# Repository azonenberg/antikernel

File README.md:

# Antikernel

This is the new development repository for the Antikernel OS.

## Project Roadmap:

In no particular order...

Eventually some of these TODOs will be broken down into tickets on the issue tracker. Need to work out some finer 
details on design first.

* The legacy Splash build system is being completely rewritten and replaced.
* We'd love to write some developer documentation and formally specify the APIs for various existing components, as 
well as writing specifications for not-yet-implemented peripherals/drivers/services
* Fix the SARATOGA L1 cache so the miss servicing latency isn't so bad.
* Reduce hazards between SARATOGA execution units so we can dual-issue a higher fraction of instructions.
* Experiment with porting Antikernel to a Xilinx Zynq SoC using both the Cortex-A9s and the FPGA.
* We should probably have a filesystem at some point.

## Stuff you might be interested in:

* Project IRC channel: #antikernel on Freenode
* Original PhD thesis: https://pqdtopen.proquest.com/doc/1705867421.html?FMT=ABS
* CHES 2016 paper: https://eprint.iacr.org/2016/550
* CHES 2016 slides: http://www.chesworkshop.org/ches2016/presentations/0918%20Session%205/CHES2016_Session5_2.pdf
* CHES 2016 video: https://www.iacr.org/cryptodb/data/paper.php?pubkey=27850
* TODO: S4x17 slides and video once posted
* Build system: https://github.com/azonenberg/splash-build-system/

## NOTES

The "legacy-*" directories contain a raw export of the old Subversion repository. This will all get moved elsewhere,
possibly to separate repositories, during the upcoming restructuring.

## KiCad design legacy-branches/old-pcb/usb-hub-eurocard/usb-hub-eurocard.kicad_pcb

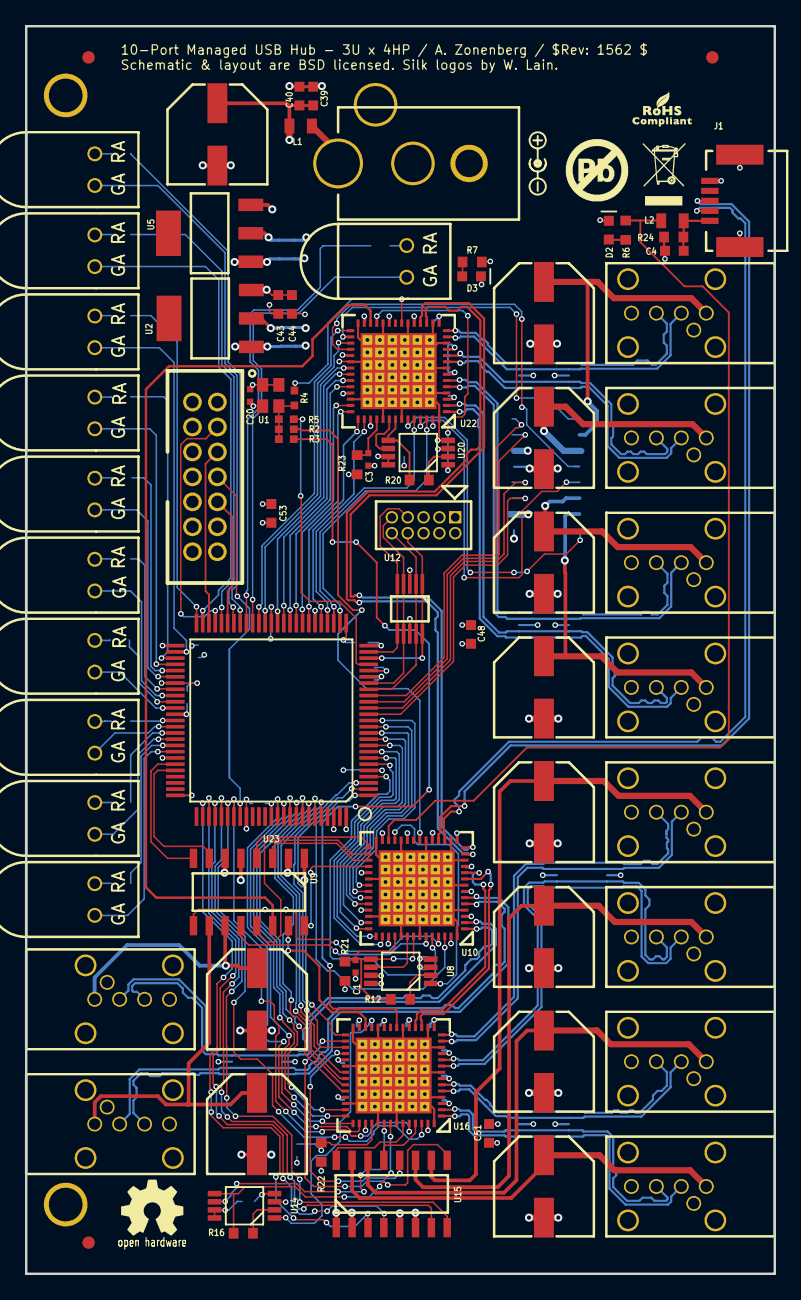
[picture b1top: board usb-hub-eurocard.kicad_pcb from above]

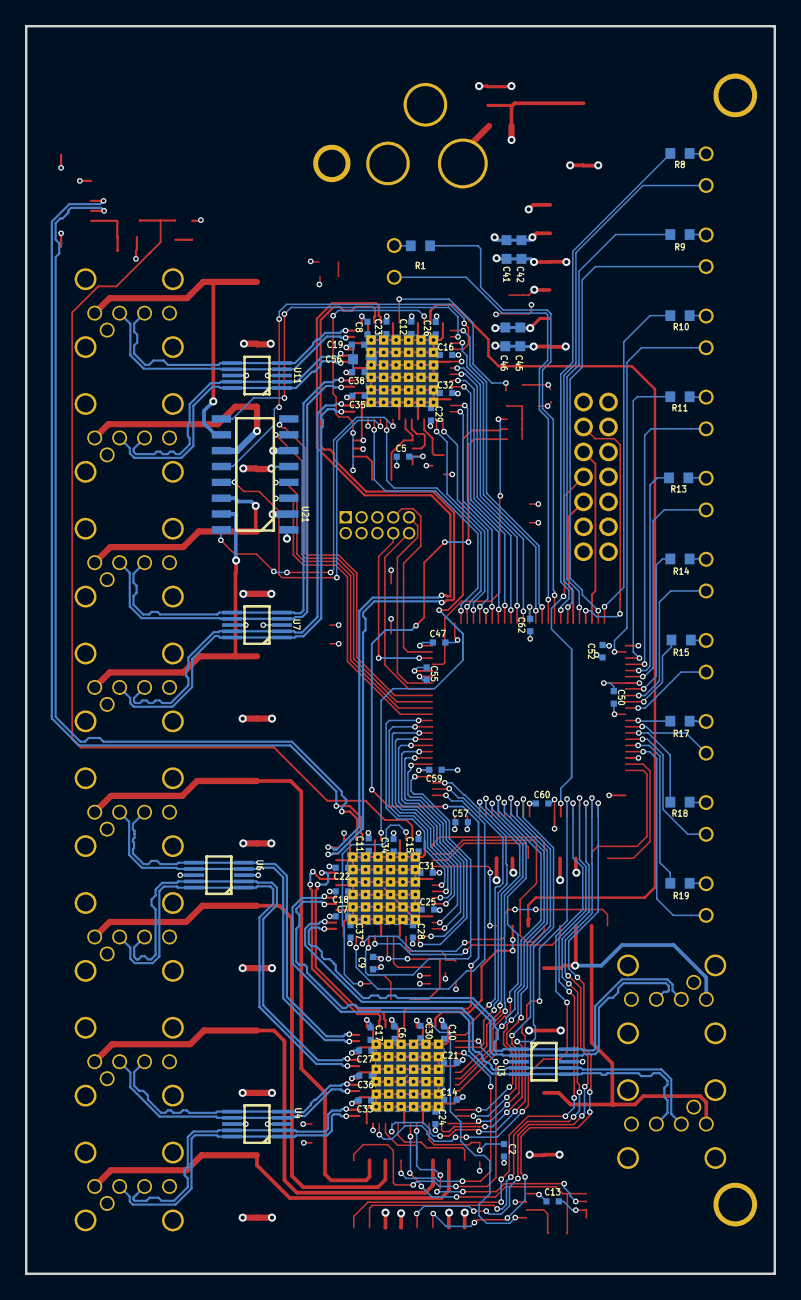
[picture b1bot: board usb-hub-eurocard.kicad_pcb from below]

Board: 4 copper layers, 60.0 x 100.0 mm, 145 parts (64 on the bottom side), 166 nets.

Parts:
C1, C2, C3, C5, C6, C7, C8, C9, C10, C11, C12, C13, C14, C15, C16, C17, C18, C19, C20, C21, C22, C23, C24, C25, C26, C27, C28, C29, C30, C31, C32, C33, C34, C35, C36, C37, C38, C47, C50, C52, C55, C57, C59, C60, C62: 0.1 uF; EIA_0402_CAP_NOSILK
C4, C39, C40, C41, C42, C43, C44, C45, C46, C48, C51, C53, C56: 4.7 uF; EIA_0603_CAP_NOSILK
C49, C54, C58, C61, C63, C64, C65, C66, C67, C68, C69: 150 uF; CAP_AL_6.3MM_SMT
D1, D4, D5, D6, D7, D8, D9, D10, D11, D12, D13: R/G; LED_INDICATOR_2.54MM_5MM_RG_RA
D2, D3: GREEN; EIA_0603_LED
FIDUCIAL_1MM, FIDUCIAL_1MM#2, FIDUCIAL_1MM#3: VAL**; FIDUCIAL_1MM
J1: USB; CONN_HIROSE_UX60S-MB-5ST_MINI_USB
J2, J3, J4, J5, J6, J8, J9, J10, J11, J12: USB_2; CONN_FCI_USB_73725-0110BLF
J7: XILINX_JTAG; XILINX_JTAG_PTH_MOLEX_0878311420
K1: DC JACK; CONN_CUI_PJ-058BH_HIPWR_BARREL_NOSLOT
L1: 120R 5A; EIA_0805_INDUCTOR_NOSILK
L2: 600R; EIA_0805_INDUCTOR_NOSILK
MECHANICAL_EUROCARD_3U_FRONTHOLES: VAL**; MECHANICAL_EUROCARD_3U_FRONTHOLES
P1: CONN_10; CONN_HEADER_1.27MM_2X5
R1, R6, R7, R8, R9, R10, R11, R13, R14, R15, R17, R18, R19: 470; EIA_0603_RES_NOSILK
R2, R3, R4, R5: 33; EIA_0402_RES_NOSILK
R12, R16, R20: 1K; EIA_0603_RES_NOSILK
R21, R22, R23, R24: 100K; EIA_0603_RES_NOSILK
U1: 24 MHz; OSCILLATOR_2.5x2.0
U2: LDO1117-18; SOT223-4
U3, U4, U6, U7, U11, U12: RCLAMP0514M; SOP_10_0.5MM_3MM
U5: LDO1117-33; SOT223-4
U8, U14, U20: 25LC080; SOP_8_0.5MM_3MM
U9, U15, U21: TPS2044BD; SOIC_16_3.9MM
U10, U16, U22: CY7C65631; QFN_56_0.5MM_8x8MM
U23: XC2C128-7VQG100C; QFP_100_0.5MM

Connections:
/1V8: C45.1, C46.1, C47.1, C50.1, U2.2, U23.26, U23.57
/3V3: C5.1, C6.1, C7.1, C8.1, C9.1, C10.1, C11.1, C12.1, C13.1, C14.1, C15.1, C16.1, C17.1, C18.1, C19.1, C20.1, C21.1, C22.1, C23.1, C24.1, C25.1, C26.1, C27.1, C28.1, C29.1, C30.1, C31.1, C32.1, C33.1, C34.1, C35.1, C36.1, C37.1, C38.1, C41.1, C42.1, C43.1, C44.1, C48.1, C51.1, C52.1, C53.1, C55.1, C56.1, C57.1, C59.1, C60.1, C62.1, J7.2, P1.3, P1.4, R21.1, R22.1, R23.1, U1.1, U1.4, U2.3, U3.3, U4.3, U5.2, U6.3, U7.3, U8.3, U8.7, U8.8, U10.3, U10.7, U10.11, U10.15, U10.19, U10.23, U10.27, U10.33, U10.39, U10.45, U10.55, U11.3, U12.3, U14.3, U14.7, U14.8, U16.3, U16.7, U16.11, U16.15, U16.19, U16.23, U16.27, U16.33, U16.39, U16.45, U16.55, U20.3, U20.7, U20.8, U22.3, U22.7, U22.11, U22.15, U22.19, U22.23, U22.27, U22.33, U22.39, U22.45, U22.55, U23.5, U23.20, U23.38, U23.51, U23.88, U23.98
/5V0: C39.1, C40.1, C49.1, L1.1, P1.1, P1.2, R7.1, U5.3, U9.2, U9.6, U15.2, U15.6, U21.2, U21.6
/5V0_RAW: K1.1, L1.2
/CLK_24MHZ: R2.1, R3.1, R4.1, R5.1, U1.3
/CLK_24MHZ_1: R2.2, U10.21
/CLK_24MHZ_2: R3.2, U16.21
/CLK_24MHZ_3: R4.2, U22.21
/CLK_24MHZ_4: R5.2, U23.22
/EXPANSION_SPI_CS_N: P1.7, U12.5, U12.6, U23.24
/EXPANSION_SPI_MISO: P1.10, U12.2, U12.9, U23.18
/EXPANSION_SPI_MOSI: P1.9, U12.4, U12.7, U23.19
/EXPANSION_SPI_SCK: P1.8, U12.1, U12.10, U23.23
/GND: C1.1, C2.1, C3.1, C4.2, C5.2, C6.2, C7.2, C8.2, C9.2, C10.2, C11.2, C12.2, C13.2, C14.2, C15.2, C16.2, C17.2, C18.2, C19.2, C20.2, C21.2, C22.2, C23.2, C24.2, C25.2, C26.2, C27.2, C28.2, C29.2, C30.2, C31.2, C32.2, C33.2, C34.2, C35.2, C36.2, C37.2, C38.2, C39.2, C40.2, C41.2, C42.2, C43.2, C44.2, C45.2, C46.2, C47.2, C48.2, C49.2, C50.2, C51.2, C52.2, C53.2, C54.2, C55.2, C56.2, C57.2, C58.2, C59.2, C60.2, C61.2, C62.2, C63.2, C64.2, C65.2, C66.2, C67.2, C68.2, C69.2, D2.2, D3.2, J1.5, J1.6, J1.7, J2.4, J3.4, J4.4, J5.4, J6.4, J7.3, J7.5, J7.7, J7.9, J7.11, J8.4, J9.4, J10.4, J11.4, J12.4, K1.2, P1.5, P1.6, R24.2, U1.2, U2.1, U3.8, U4.8, U5.1, U6.8, U7.8, U8.4, U9.1, U9.5, U10.4, U10.8, U10.12, U10.16, U10.20, U10.24, U10.28, U10.34, U10.40, U10.47, U10.50, U10.56, U10.PAD, U11.8, U12.8, U14.4, U15.1, U15.5, U16.4, U16.8, U16.12, U16.16, U16.20, U16.24, U16.28, U16.34, U16.40, U16.47, U16.50, U16.56, U16.PAD, U20.4, U21.1, U21.5, U22.4, U22.8, U22.12, U22.16, U22.20, U22.24, U22.28, U22.34, U22.40, U22.47, U22.50, U22.56, U22.PAD, U23.21, U23.25, U23.31, U23.62, U23.69, U23.75, U23.84, U23.100
/HOST_D_N: J1.2, U10.17
/HOST_D_P: J1.3, U10.18
/HUB1_DATA_N: U10.9, U16.17
/HUB1_DATA_P: U10.10, U16.18
/HUB1_FAULT: U10.38, U23.10
/HUB1_OVR_N: U9.16, U10.32
/HUB1_PWR_N: U9.3, U10.31
/HUB1_STATUS: U10.37, U23.11
/HUB1_VBUS: U9.15, U16.26
/HUB2_DATA_N: U10.13, U22.17
/HUB2_DATA_P: U10.14, U22.18
/HUB2_FAULT: U10.36, U23.12
/HUB2_OVR_N: U9.13, U10.30
/HUB2_PWR_N: U9.4, U10.29
/HUB2_STATUS: U10.35, U23.13
/HUB2_VBUS: U9.14, U22.26
/JTAG_TCK: J7.6, U23.48
/JTAG_TDI: J7.10, U23.45
/JTAG_TDO: J7.8, U23.83
/JTAG_TMS: J7.4, U23.47
/PORT1_DATA_N: J2.2, U3.1, U3.10, U10.1
/PORT1_DATA_P: J2.3, U3.2, U3.9, U10.2
/PORT1_FAULT: U10.44, U23.6
/PORT1_LED_N: D4.2, U23.44
/PORT1_LED_P: R8.1, U23.43
/PORT1_OVR_N: U9.12, U10.51
/PORT1_PWR_N: U10.52, U23.4
/PORT1_STATUS: U10.43, U23.7
/PORT1_VBUS: C54.1, J2.1, U9.11
/PORT2_DATA_N: J3.2, U3.4, U3.7, U10.5
/PORT2_DATA_P: J3.3, U3.5, U3.6, U10.6
/PORT2_FAULT: U10.42, U23.8
/PORT2_LED_N: D5.2, U23.49
/PORT2_LED_P: R9.1, U23.46
/PORT2_OVR_N: U9.9, U10.53
/PORT2_PWR_N: U10.54, U23.1
/PORT2_STATUS: U10.41, U23.9
/PORT2_VBUS: C58.1, J3.1, U9.10
/PORT3_DATA_N: J4.2, U4.1, U4.10, U16.1
/PORT3_DATA_P: J4.3, U4.2, U4.9, U16.2
/PORT3_FAULT: U16.44, U23.89
/PORT3_LED_N: D6.2, U23.52
/PORT3_LED_P: R10.1, U23.50
/PORT3_OVR_N: U15.16, U16.51
/PORT3_PWR_N: U16.52, U23.82
/PORT3_STATUS: U16.43, U23.90
/PORT3_VBUS: C61.1, J4.1, U15.15
/PORT4_DATA_N: J5.2, U4.4, U4.7, U16.5
/PORT4_DATA_P: J5.3, U4.5, U4.6, U16.6
/PORT4_FAULT: U16.42, U23.91
/PORT4_LED_N: D7.2, U23.54
/PORT4_LED_P: R11.1, U23.53
/PORT4_OVR_N: U15.13, U16.53
/PORT4_PWR_N: U16.54, U23.81
/PORT4_STATUS: U16.41, U23.92
/PORT4_VBUS: C63.1, J5.1, U15.14
/PORT5_DATA_N: J6.2, U6.1, U6.10, U16.9
/PORT5_DATA_P: J6.3, U6.2, U6.9, U16.10
/PORT5_FAULT: U16.38, U23.93
/PORT5_LED_N: D8.2, U23.56
/PORT5_LED_P: R13.1, U23.55
/PORT5_OVR_N: U15.12, U16.32
/PORT5_PWR_N: U16.31, U23.3
/PORT5_STATUS: U16.37, U23.94
/PORT5_VBUS: C64.1, J6.1, U15.11
/PORT6_DATA_N: J8.2, U6.4, U6.7, U16.13
/PORT6_DATA_P: J8.3, U6.5, U6.6, U16.14
/PORT6_FAULT: U16.36, U23.95
/PORT6_LED_N: D9.2, U23.59
/PORT6_LED_P: R14.1, U23.58
/PORT6_OVR_N: U15.9, U16.30
/PORT6_PWR_N: U16.29, U23.2
/PORT6_STATUS: U16.35, U23.96
/PORT6_VBUS: C65.1, J8.1, U15.10
/PORT7_DATA_N: J9.2, U7.1, U7.10, U22.1
/PORT7_DATA_P: J9.3, U7.2, U7.9, U22.2
/PORT7_FAULT: U22.44, U23.29
/PORT7_LED_N: D10.2, U23.61
/PORT7_LED_P: R15.1, U23.60
/PORT7_OVR_N: U21.16, U22.51
/PORT7_PWR_N: U22.52, U23.28
/PORT7_STATUS: U22.43, U23.30
/PORT7_VBUS: C66.1, J9.1, U21.15
/PORT8_DATA_N: J10.2, U7.4, U7.7, U22.5
/PORT8_DATA_P: J10.3, U7.5, U7.6, U22.6
/PORT8_FAULT: U22.42, U23.32
/PORT8_LED_N: D11.2, U23.64
/PORT8_LED_P: R17.1, U23.63
/PORT8_OVR_N: U21.13, U22.53
/PORT8_PWR_N: U22.54, U23.27
/PORT8_STATUS: U22.41, U23.33
/PORT8_VBUS: C67.1, J10.1, U21.14
/PORT9_DATA_N: J11.2, U11.1, U11.10, U22.9
/PORT9_DATA_P: J11.3, U11.2, U11.9, U22.10
/PORT9_FAULT: U22.38, U23.34
/PORT9_LED_N: D12.2, U23.66
/PORT9_LED_P: R18.1, U23.65
/PORT9_OVR_N: U21.12, U22.32
/PORT9_PWR_N: U22.31, U23.39
/PORT9_STATUS: U22.37, U23.35
/PORT9_VBUS: C68.1, J11.1, U21.11
/PORT10_DATA_N: J12.2, U11.4, U11.7, U22.13
/PORT10_DATA_P: J12.3, U11.5, U11.6, U22.14
/PORT10_FAULT: U22.36, U23.36
/PORT10_LED_N: D13.2, U23.68
/PORT10_LED_P: R19.1, U23.67
/PORT10_OVR_N: U21.9, U22.30
/PORT10_PWR_N: U22.29, U23.40
/PORT10_STATUS: U22.35, U23.37
/PORT10_VBUS: C69.1, J12.1, U21.10
/SPI_1_CS_N: U8.1, U10.25
/SPI_1_DATA: R12.2, U8.5, U10.49
/SPI_1_MISO: R12.1, U8.2
/SPI_1_SCK: U8.6, U10.48
/SPI_2_CS_N: U14.1, U16.25
/SPI_2_DATA: R16.2, U14.5, U16.49
/SPI_2_MISO: R16.1, U14.2
/SPI_2_SCK: U14.6, U16.48
/SPI_3_CS_N: U20.1, U22.25
/SPI_3_DATA: R20.2, U20.5, U22.49
/SPI_3_MISO: R20.1, U20.2
/SPI_3_SCK: U20.6, U22.48
/STATUS_LED_N: D1.2, U23.41
/STATUS_LED_P: R1.2, U23.42
/VBUS: C4.1, J1.1, L2.2, R24.1
/VBUS1_EN_N: U9.7, U23.71
/VBUS2_EN_N: U9.8, U23.70
/VBUS3_EN_N: U15.3, U23.77
/VBUS4_EN_N: U15.4, U23.78
/VBUS5_EN_N: U15.7, U23.79
/VBUS6_EN_N: U15.8, U23.80
/VBUS7_EN_N: U21.3, U23.14
/VBUS8_EN_N: U21.4, U23.15
/VBUS9_EN_N: U21.7, U23.16
/VBUS10_EN_N: U21.8, U23.17
/VBUS_FILTERED: L2.1, R6.1, U10.26
unnamed: C1.2, R21.2, U10.46
unnamed: C2.2, R22.2, U16.46
unnamed: C3.2, R23.2, U22.46
unnamed: D1.1, R1.1
unnamed: D2.1, R6.2
unnamed: D3.1, R7.2
unnamed: D4.1, R8.2
unnamed: D5.1, R9.2
unnamed: D6.1, R10.2
unnamed: D7.1, R11.2
unnamed: D8.1, R13.2
unnamed: D9.1, R14.2
unnamed: D10.1, R15.2
unnamed: D11.1, R17.2
unnamed: D12.1, R18.2
unnamed: D13.1, R19.2

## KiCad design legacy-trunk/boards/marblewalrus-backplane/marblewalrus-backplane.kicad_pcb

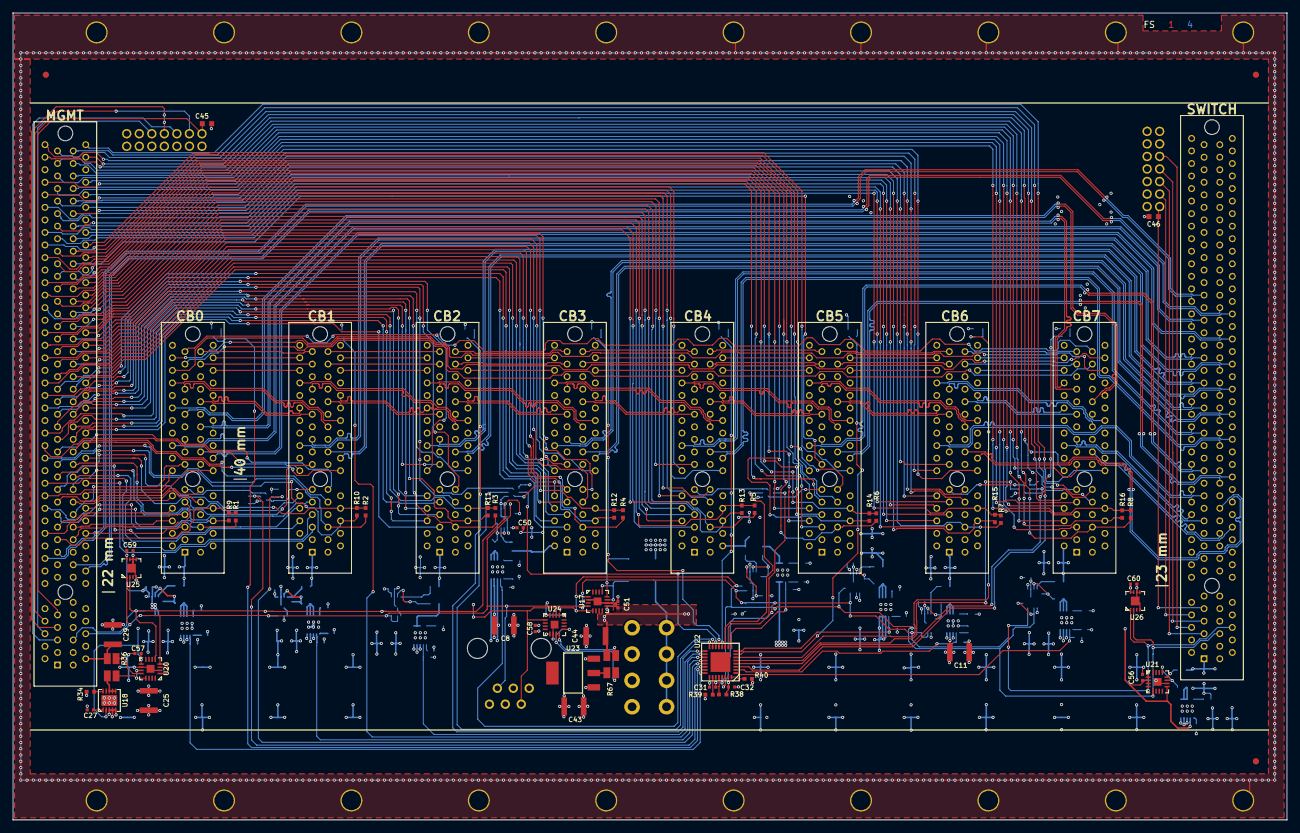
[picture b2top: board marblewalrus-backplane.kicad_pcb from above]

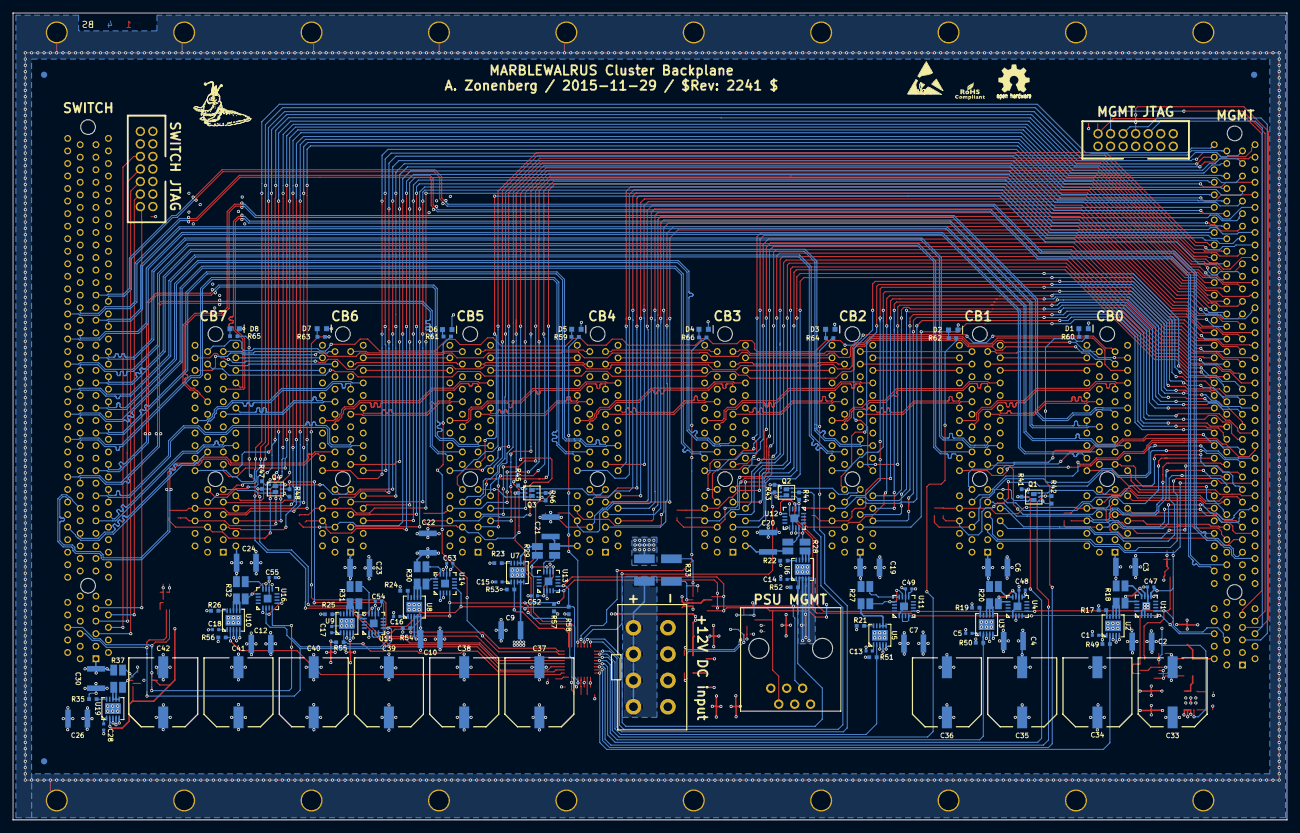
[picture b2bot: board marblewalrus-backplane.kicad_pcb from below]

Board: 4 copper layers, 203.2 x 128.7 mm, 195 parts (123 on the bottom side), 336 nets.

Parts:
C1, C5, C13, C14, C15, C16, C17, C18, C27, C28: 470 pF; EIA_0402_CAP_NOSILK
C2, C3, C4, C6, C7, C8, C9, C10, C11, C12, C19, C20, C21, C22, C23, C24, C25, C26, C29, C30: 4.7 uF 35V; EIA_1210_CAP_NOSILK
C31, C32, C47, C48, C49, C50, C51, C52, C53, C54, C55, C56, C57, C58, C59, C60: 0.1 uF; EIA_0402_CAP_NOSILK
C33, C34, C35, C36, C37, C38, C39, C40, C41, C42: 470 uF; CAP_AL_10MM_SMT
C43, C44: 4.7 uF; EIA_1210_CAP_NOSILK
C45, C46: 4.7 uF; EIA_0603_CAP_NOSILK
D1, D2, D3, D4, D5, D6, D7, D8: GREEN; EIA_0603_LED
FIDUCIAL_1MM, FIDUCIAL_1MM#2, FIDUCIAL_1MM#3, FIDUCIAL_1MM#4, FIDUCIAL_1MM#5, FIDUCIAL_1MM#6: VAL**; FIDUCIAL_1MM
J1, J2, J3, J4, J5, J6, J7, J8: CONN_MW_COMPUTE_BACKPLANE; CONN_PCIE_X4_FCI_10018783_10201TLF
J9: CONN_MW_MGMT_BACKPLANE; CONN_PCIE_X16_FCI_10018783_10203TLF
J10: CONN_MW_SWITCH_BACKPLANE; CONN_PCIE_X16_FCI_10018783_10203TLF
J11: CONN_MW_12V; CONN_MW_12V_VERTICAL
J12: CONN_MW_PSU_MGMT; CONN_RJ11_ASSMANN_A-2014-1-4-N-T-R
J13, J14: XILINX_JTAG; XILINX_JTAG_PTH_MOLEX_0878311420
MH1, MH2, MH3, MH4, MH5, MH6, MH7, MH8, MH9, MH10: M; MECHANICAL_EUROCARD_3U_BACKPLANE_SEG
Q1, Q2, Q3, Q4: SSM6N58NU; DFN_6_0.65MM_2x2MM_GDS
R1, R2, R3, R4, R5, R6, R7, R8, R9, R10, R11, R12, R13, R14, R15, R16, R57, R58: 1K; EIA_0402_RES_NOSILK
R17, R19, R21, R22, R23, R24, R25, R26, R34, R35: 100K; EIA_0402_RES_NOSILK
R18, R20, R27, R28, R29, R30, R31, R32, R36, R37: 20 m; OHMITE_LVK12
R33: 2 m; OHMITE_LVK25
R38, R39, R40, R41, R42, R43, R44, R45, R46, R47, R48, R49, R50, R51, R52, R53, R54, R55, R56: 10K; EIA_0402_RES_NOSILK
R59, R60, R61, R62, R63, R64, R65, R66: 330; EIA_0402_RES_NOSILK
R67: 50 m; OHMITE_LVK12
U1, U4, U11, U12, U13, U14, U15, U16, U17, U20, U21, U24: INA230; QFN_16_0.5MM_3x3MM
U2, U3, U5, U6, U7, U8, U9, U10, U18, U19: TPS259260; DFN_10_0.5MM_3x3MM
U22: TCA6424A; QFN_32_0.5MM_5x5MM
U23: LDO1117-33; SOT223-4
U25, U26: PCT2075TP; DFN_8_0.5MM_3x3MM

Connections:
/Compute Blade Core/12V0_CB0: C3.2, J1.A1, J1.A2, J1.A3, J1.B1, J1.B2, J1.B3, R18.2
/Compute Blade Core/12V0_CB1: C6.2, J2.A1, J2.A2, J2.A3, J2.B1, J2.B2, J2.B3, R20.2
/Compute Blade Core/12V0_CB2: C19.2, J3.A1, J3.A2, J3.A3, J3.B1, J3.B2, J3.B3, R27.2
/Compute Blade Core/12V0_CB3: C20.2, J4.A1, J4.A2, J4.A3, J4.B1, J4.B2, J4.B3, R28.2
/Compute Blade Core/12V0_CB4: C21.2, J5.A1, J5.A2, J5.A3, J5.B1, J5.B2, J5.B3, R29.2
/Compute Blade Core/12V0_CB5: C22.2, J6.A1, J6.A2, J6.A3, J6.B1, J6.B2, J6.B3, R30.2
/Compute Blade Core/12V0_CB6: C23.2, J7.A1, J7.A2, J7.A3, J7.B1, J7.B2, J7.B3, R31.2
/Compute Blade Core/12V0_CB7: C24.2, J8.A1, J8.A2, J8.A3, J8.B1, J8.B2, J8.B3, R32.2
/Compute Blade Core/CB0_ETH_RX_N: J1.A17, J10.A53
/Compute Blade Core/CB0_ETH_RX_P: J1.A16, J10.A52
/Compute Blade Core/CB0_ETH_TX_N: J1.B15, J10.B51
/Compute Blade Core/CB0_ETH_TX_P: J1.B14, J10.B50
/Compute Blade Core/CB0_GPIO_0: J1.B9, J9.B25
/Compute Blade Core/CB0_GPIO_1: J1.B11, J9.A25
/Compute Blade Core/CB0_GPIO_2: J1.B12, J9.B26
/Compute Blade Core/CB0_GPIO_3: J1.A12, J9.A26
/Compute Blade Core/CB0_GPIO_VDD: J1.B8, J9.A19, R1.1, R9.1
/Compute Blade Core/CB0_I2C_SCL: J1.B5, J9.A24, R1.2
/Compute Blade Core/CB0_I2C_SDA: J1.B6, J9.A23, R9.2
/Compute Blade Core/CB0_JTAG_VDD: J1.A9, J9.B19
/Compute Blade Core/CB0_RESET_N: J1.A11, Q1.D1
/Compute Blade Core/CB0_TCK: J1.A5, J9.B20
/Compute Blade Core/CB0_TDI: J1.A6, J9.B21
/Compute Blade Core/CB0_TDO: J1.A7, J9.A20
/Compute Blade Core/CB0_TMS: J1.A8, J9.A21
/Compute Blade Core/CB0_UART_RX: J1.A10, J9.B24
/Compute Blade Core/CB0_UART_TX: J1.A13, J9.B23
/Compute Blade Core/CB1_ETH_RX_N: J2.A17, J10.A48
/Compute Blade Core/CB1_ETH_RX_P: J2.A16, J10.A47
/Compute Blade Core/CB1_ETH_TX_N: J2.B15, J10.B46
/Compute Blade Core/CB1_ETH_TX_P: J2.B14, J10.B45
/Compute Blade Core/CB1_GPIO_0: J2.B9, J9.B33
/Compute Blade Core/CB1_GPIO_1: J2.B11, J9.A33
/Compute Blade Core/CB1_GPIO_2: J2.B12, J9.B34
/Compute Blade Core/CB1_GPIO_3: J2.A12, J9.A34
/Compute Blade Core/CB1_GPIO_VDD: J2.B8, J9.A27, R2.1, R10.1
/Compute Blade Core/CB1_I2C_SCL: J2.B5, J9.A32, R2.2
/Compute Blade Core/CB1_I2C_SDA: J2.B6, J9.A31, R10.2
/Compute Blade Core/CB1_JTAG_VDD: J2.A9, J9.B27
/Compute Blade Core/CB1_RESET_N: J2.A11, Q1.D2
/Compute Blade Core/CB1_TCK: J2.A5, J9.B28
/Compute Blade Core/CB1_TDI: J2.A6, J9.B29
/Compute Blade Core/CB1_TDO: J2.A7, J9.A28
/Compute Blade Core/CB1_TMS: J2.A8, J9.A29
/Compute Blade Core/CB1_UART_RX: J2.A10, J9.B32
/Compute Blade Core/CB1_UART_TX: J2.A13, J9.B31
/Compute Blade Core/CB2_ETH_RX_N: J3.A17, J10.A44
/Compute Blade Core/CB2_ETH_RX_P: J3.A16, J10.A43
/Compute Blade Core/CB2_ETH_TX_N: J3.B15, J10.B42
/Compute Blade Core/CB2_ETH_TX_P: J3.B14, J10.B41
/Compute Blade Core/CB2_GPIO_0: J3.B9, J9.B41
/Compute Blade Core/CB2_GPIO_1: J3.B11, J9.A41
/Compute Blade Core/CB2_GPIO_2: J3.B12, J9.B42
/Compute Blade Core/CB2_GPIO_3: J3.A12, J9.A42
/Compute Blade Core/CB2_GPIO_VDD: J3.B8, J9.A35, R3.1, R11.1
/Compute Blade Core/CB2_I2C_SCL: J3.B5, J9.A40, R3.2
/Compute Blade Core/CB2_I2C_SDA: J3.B6, J9.A39, R11.2
/Compute Blade Core/CB2_JTAG_VDD: J3.A9, J9.B35
/Compute Blade Core/CB2_RESET_N: J3.A11, Q2.D1
/Compute Blade Core/CB2_TCK: J3.A5, J9.B36
/Compute Blade Core/CB2_TDI: J3.A6, J9.B37
/Compute Blade Core/CB2_TDO: J3.A7, J9.A36
/Compute Blade Core/CB2_TMS: J3.A8, J9.A37
/Compute Blade Core/CB2_UART_RX: J3.A10, J9.B40
/Compute Blade Core/CB2_UART_TX: J3.A13, J9.B39
/Compute Blade Core/CB3_ETH_RX_N: J4.A17, J10.A40
/Compute Blade Core/CB3_ETH_RX_P: J4.A16, J10.A39
/Compute Blade Core/CB3_ETH_TX_N: J4.B15, J10.B38
/Compute Blade Core/CB3_ETH_TX_P: J4.B14, J10.B37
/Compute Blade Core/CB3_GPIO_0: J4.B9, J9.B49
/Compute Blade Core/CB3_GPIO_1: J4.B11, J9.A49
/Compute Blade Core/CB3_GPIO_2: J4.B12, J9.B50
/Compute Blade Core/CB3_GPIO_3: J4.A12, J9.A50
/Compute Blade Core/CB3_GPIO_VDD: J4.B8, J9.A43, R4.1, R12.1
/Compute Blade Core/CB3_I2C_SCL: J4.B5, J9.A48, R4.2
/Compute Blade Core/CB3_I2C_SDA: J4.B6, J9.A47, R12.2
/Compute Blade Core/CB3_JTAG_VDD: J4.A9, J9.B43
/Compute Blade Core/CB3_RESET_N: J4.A11, Q2.D2
/Compute Blade Core/CB3_TCK: J4.A5, J9.B44
/Compute Blade Core/CB3_TDI: J4.A6, J9.B45
/Compute Blade Core/CB3_TDO: J4.A7, J9.A44
/Compute Blade Core/CB3_TMS: J4.A8, J9.A45
/Compute Blade Core/CB3_UART_RX: J4.A10, J9.B48
/Compute Blade Core/CB3_UART_TX: J4.A13, J9.B47
/Compute Blade Core/CB4_ETH_RX_N: J5.A17, J10.A36
/Compute Blade Core/CB4_ETH_RX_P: J5.A16, J10.A35
/Compute Blade Core/CB4_ETH_TX_N: J5.B15, J10.B34
/Compute Blade Core/CB4_ETH_TX_P: J5.B14, J10.B33
/Compute Blade Core/CB4_GPIO_0: J5.B9, J9.B57
/Compute Blade Core/CB4_GPIO_1: J5.B11, J9.A57
/Compute Blade Core/CB4_GPIO_2: J5.B12, J9.B58
/Compute Blade Core/CB4_GPIO_3: J5.A12, J9.A58
/Compute Blade Core/CB4_GPIO_VDD: J5.B8, J9.A51, R5.1, R13.1
/Compute Blade Core/CB4_I2C_SCL: J5.B5, J9.A56, R5.2
/Compute Blade Core/CB4_I2C_SDA: J5.B6, J9.A55, R13.2
/Compute Blade Core/CB4_JTAG_VDD: J5.A9, J9.B51
/Compute Blade Core/CB4_RESET_N: J5.A11, Q3.D1
/Compute Blade Core/CB4_TCK: J5.A5, J9.B52
/Compute Blade Core/CB4_TDI: J5.A6, J9.B53
/Compute Blade Core/CB4_TDO: J5.A7, J9.A52
/Compute Blade Core/CB4_TMS: J5.A8, J9.A53
/Compute Blade Core/CB4_UART_RX: J5.A10, J9.B56
/Compute Blade Core/CB4_UART_TX: J5.A13, J9.B55
/Compute Blade Core/CB5_ETH_RX_N: J6.A17, J10.A30
/Compute Blade Core/CB5_ETH_RX_P: J6.A16, J10.A29
/Compute Blade Core/CB5_ETH_TX_N: J6.B15, J10.B28
/Compute Blade Core/CB5_ETH_TX_P: J6.B14, J10.B27
/Compute Blade Core/CB5_GPIO_0: J6.B9, J9.B65
/Compute Blade Core/CB5_GPIO_1: J6.B11, J9.A65
/Compute Blade Core/CB5_GPIO_2: J6.B12, J9.B66
/Compute Blade Core/CB5_GPIO_3: J6.A12, J9.A66
/Compute Blade Core/CB5_GPIO_VDD: J6.B8, J9.A59, R6.1, R14.1
/Compute Blade Core/CB5_I2C_SCL: J6.B5, J9.A64, R6.2
/Compute Blade Core/CB5_I2C_SDA: J6.B6, J9.A63, R14.2
/Compute Blade Core/CB5_JTAG_VDD: J6.A9, J9.B59
/Compute Blade Core/CB5_RESET_N: J6.A11, Q3.D2
/Compute Blade Core/CB5_TCK: J6.A5, J9.B60
/Compute Blade Core/CB5_TDI: J6.A6, J9.B61
/Compute Blade Core/CB5_TDO: J6.A7, J9.A60
/Compute Blade Core/CB5_TMS: J6.A8, J9.A61
/Compute Blade Core/CB5_UART_RX: J6.A10, J9.B64
/Compute Blade Core/CB5_UART_TX: J6.A13, J9.B63
/Compute Blade Core/CB6_ETH_RX_N: J7.A17, J10.A26
/Compute Blade Core/CB6_ETH_RX_P: J7.A16, J10.A25
/Compute Blade Core/CB6_ETH_TX_N: J7.B15, J10.B24
/Compute Blade Core/CB6_ETH_TX_P: J7.B14, J10.B23
/Compute Blade Core/CB6_GPIO_0: J7.B9, J9.B73
/Compute Blade Core/CB6_GPIO_1: J7.B11, J9.A73
/Compute Blade Core/CB6_GPIO_2: J7.B12, J9.B74
/Compute Blade Core/CB6_GPIO_3: J7.A12, J9.A74
/Compute Blade Core/CB6_GPIO_VDD: J7.B8, J9.A67, R7.1, R15.1
/Compute Blade Core/CB6_I2C_SCL: J7.B5, J9.A72, R7.2
/Compute Blade Core/CB6_I2C_SDA: J7.B6, J9.A71, R15.2
/Compute Blade Core/CB6_JTAG_VDD: J7.A9, J9.B67
/Compute Blade Core/CB6_RESET_N: J7.A11, Q4.D1
/Compute Blade Core/CB6_TCK: J7.A5, J9.B68
/Compute Blade Core/CB6_TDI: J7.A6, J9.B69
/Compute Blade Core/CB6_TDO: J7.A7, J9.A68
/Compute Blade Core/CB6_TMS: J7.A8, J9.A69
/Compute Blade Core/CB6_UART_RX: J7.A10, J9.B72
/Compute Blade Core/CB6_UART_TX: J7.A13, J9.B71
/Compute Blade Core/CB7_ETH_RX_N: J8.A17, J10.A22
/Compute Blade Core/CB7_ETH_RX_P: J8.A16, J10.A21
/Compute Blade Core/CB7_ETH_TX_N: J8.B15, J10.B20
/Compute Blade Core/CB7_ETH_TX_P: J8.B14, J10.B19
/Compute Blade Core/CB7_GPIO_0: J8.B9, J9.B81
/Compute Blade Core/CB7_GPIO_1: J8.B11, J9.A81
/Compute Blade Core/CB7_GPIO_2: J8.B12, J9.B82
/Compute Blade Core/CB7_GPIO_3: J8.A12, J9.A82
/Compute Blade Core/CB7_GPIO_VDD: J8.B8, J9.A75, R8.1, R16.1
/Compute Blade Core/CB7_I2C_SCL: J8.B5, J9.A80, R8.2
/Compute Blade Core/CB7_I2C_SDA: J8.B6, J9.A79, R16.2
/Compute Blade Core/CB7_JTAG_VDD: J8.A9, J9.B75
/Compute Blade Core/CB7_RESET_N: J8.A11, Q4.D2
/Compute Blade Core/CB7_TCK: J8.A5, J9.B76
/Compute Blade Core/CB7_TDI: J8.A6, J9.B77
/Compute Blade Core/CB7_TDO: J8.A7, J9.A76
/Compute Blade Core/CB7_TMS: J8.A8, J9.A77
/Compute Blade Core/CB7_UART_RX: J8.A10, J9.B80
/Compute Blade Core/CB7_UART_TX: J8.A13, J9.B79
/Compute Blade Core/ETH8_RX_N: J9.A17, J10.A57
/Compute Blade Core/ETH8_RX_P: J9.A16, J10.A56
/Compute Blade Core/ETH8_TX_N: J9.B15, J10.B55
/Compute Blade Core/ETH8_TX_P: J9.B14, J10.B54
/Compute Blade Core/GND: C1.1, C2.2, C3.1, C4.2, C5.1, C6.1, C7.2, C8.2, C9.2, C10.2, C11.2, C12.2, C13.1, C14.1, C15.1, C16.1, C17.1, C18.1, C19.1, C20.1, C21.1, C22.1, C23.1, C24.1, C25.2, C26.2, C27.1, C28.1, C29.1, C30.1, C31.2, C32.2, C33.2, C34.2, C35.2, C36.2, C37.2, C38.2, C39.2, C40.2, C41.2, C42.2, C43.2, C44.1, C45.2, C46.2, C47.2, C48.2, C49.2, C50.2, C51.2, C52.2, C53.2, C54.2, C55.2, C56.2, C57.2, C58.2, C59.2, C60.2, D1.1, D2.1, D3.1, D4.1, D5.1, D6.1, D7.1, D8.1, J1.A4, J1.A14, J1.A15, J1.A18, J1.A19, J1.A20, J1.A23, J1.A24, J1.A27, J1.B4, J1.B7, J1.B13, J1.B16, J1.B17, J1.B18, J1.B21, J1.B22, J1.B25, J1.B26, J1.B27, J2.A4, J2.A14, J2.A15, J2.A18, J2.A19, J2.A20, J2.A23, J2.A24, J2.A27, J2.B4, J2.B7, J2.B13, J2.B16, J2.B17, J2.B18, J2.B21, J2.B22, J2.B25, J2.B26, J2.B27, J3.A4, J3.A14, J3.A15, J3.A18, J3.A19, J3.A20, J3.A23, J3.A24, J3.A27, J3.B4, J3.B7, J3.B13, J3.B16, J3.B17, J3.B18, J3.B21, J3.B22, J3.B25, J3.B26, J3.B27, J4.A4, J4.A14, J4.A15, J4.A18, J4.A19, J4.A20, J4.A23, J4.A24, J4.A27, J4.B4, J4.B7, J4.B13, J4.B16, J4.B17, J4.B18, J4.B21, J4.B22, J4.B25, J4.B26, J4.B27, J5.A4, J5.A14, J5.A15, J5.A18, J5.A19, J5.A20, J5.A23, J5.A24, J5.A27, J5.B4, J5.B7, J5.B13, J5.B16, J5.B17, J5.B18, J5.B21, J5.B22, J5.B25, J5.B26, J5.B27, J6.A4, J6.A14, J6.A15, J6.A18, J6.A19, J6.A20, J6.A23, J6.A24, J6.A27, J6.B4, J6.B7, J6.B13, J6.B16, J6.B17, J6.B18, J6.B21, J6.B22, J6.B25, J6.B26, J6.B27, J7.A4, J7.A14, J7.A15, J7.A18, J7.A19, J7.A20, J7.A23, J7.A24, J7.A27, J7.B4, J7.B7, J7.B13, J7.B16, J7.B17, J7.B18, J7.B21, J7.B22, J7.B25, J7.B26, J7.B27, J8.A4, J8.A14, J8.A15, J8.A18, J8.A19, J8.A20, J8.A23, J8.A24, J8.A27, J8.B4, J8.B7, J8.B13, J8.B16, J8.B17, J8.B18, J8.B21, J8.B22, J8.B25, J8.B26, J8.B27, J9.A4, J9.A14, J9.A15, J9.A18, J9.A22, J9.A30, J9.A38, J9.A46, J9.A54, J9.A62, J9.A70, J9.A78, J9.B4, J9.B7, J9.B13, J9.B16, J9.B17, J9.B18, J9.B22, J9.B30, J9.B38, J9.B46, J9.B54, J9.B62, J9.B70, J9.B78, J10.A4, J10.A14, J10.A15, J10.A18, J10.A19, J10.A20, J10.A23, J10.A24, J10.A27, J10.A28, J10.A31, J10.A32, J10.A33, J10.A34, J10.A37, J10.A38, J10.A41, J10.A42, J10.A45, J10.A46, J10.A49, J10.A50, J10.A51, J10.A54, J10.A55, J10.A58, J10.A59, J10.A62, J10.A63, J10.A66, J10.A67, J10.A70, J10.A71, J10.A74, J10.A75, J10.A78, J10.A79, J10.A82, J10.B4, J10.B7, J10.B13, J10.B16, J10.B17, J10.B18, J10.B21, J10.B22, J10.B25, J10.B26, J10.B29, J10.B30, J10.B31, J10.B32, J10.B35, J10.B36, J10.B39, J10.B40, J10.B43, J10.B44, J10.B47, J10.B48, J10.B49, J10.B52, J10.B53, J10.B56, J10.B57, J10.B60, J10.B61, J10.B64, J10.B65, J10.B68, J10.B69, J10.B72, J10.B73, J10.B76, J10.B77, J10.B80, J10.B81, J10.B82, J11.1, J11.2, J11.3, J11.4, J12.1, J12.4, J12.6, J13.3, J13.5, J13.7, J13.9, J13.11, J14.3, J14.5, J14.7, J14.9, J14.11, MH1.1, MH2.1, MH3.1, MH4.1, MH5.1, MH6.1, MH7.1, MH8.1, MH9.1, MH10.1, Q1.S1, Q1.S2, Q2.S1, Q2.S2, Q3.S1, Q3.S2, Q4.S1, Q4.S2, R17.2, R19.2, R21.2, R22.2, R23.2, R24.2, R25.2, R26.2, R34.2, R35.2, R39.2, R41.2, R42.2, R43.2, R44.2, R45.2, R46.2, R47.2, R48.2, R49.2, R50.2, R51.2, R52.2, R53.2, R54.2, R55.2, R56.2, U1.1, U1.2, U1.10, U1.PAD, U2.PAD, U3.PAD, U4.1, U4.10, U4.PAD, U5.PAD, U6.PAD, U7.PAD, U8.PAD, U9.PAD, U10.PAD, U11.1, U11.10, U11.PAD, U12.1, U12.10, U12.PAD, U13.2, U13.10, U13.PAD, U14.10, U14.PAD, U15.10, U15.PAD, U16.10, U16.PAD, U17.2, U17.10, U17.PAD, U18.PAD, U19.PAD, U20.2, U20.10, U20.PAD, U21.10, U21.PAD, U22.25, U23.1, U24.10, U24.PAD, U25.4, U25.5, U25.6, U25.7, U25.PAD, U26.4, U26.5, U26.6, U26.PAD
/Compute Blade Ring Bus/CB0_GPIO_LEFT_0: J1.A28, J8.B28
/Compute Blade Ring Bus/CB0_GPIO_LEFT_1: J1.A29, J8.B29
/Compute Blade Ring Bus/CB0_GPIO_LEFT_2: J1.A30, J8.B30
/Compute Blade Ring Bus/CB0_GPIO_LEFT_3: J1.A31, J8.B31
/Compute Blade Ring Bus/CB0_TX_LEFT_N: J1.B20, J8.A26
/Compute Blade Ring Bus/CB0_TX_LEFT_P: J1.B19, J8.A25
/Compute Blade Ring Bus/CB0_TX_RIGHT_N: J1.B24, J2.A22
/Compute Blade Ring Bus/CB0_TX_RIGHT_P: J1.B23, J2.A21
/Compute Blade Ring Bus/CB1_GPIO_LEFT_0: J1.B28, J2.A28
/Compute Blade Ring Bus/CB1_GPIO_LEFT_1: J1.B29, J2.A29
/Compute Blade Ring Bus/CB1_GPIO_LEFT_2: J1.B30, J2.A30
/Compute Blade Ring Bus/CB1_GPIO_LEFT_3: J1.B31, J2.A31
/Compute Blade Ring Bus/CB1_TX_LEFT_N: J1.A26, J2.B20
/Compute Blade Ring Bus/CB1_TX_LEFT_P: J1.A25, J2.B19
/Compute Blade Ring Bus/CB1_TX_RIGHT_N: J2.B24, J3.A22
/Compute Blade Ring Bus/CB1_TX_RIGHT_P: J2.B23, J3.A21
/Compute Blade Ring Bus/CB2_GPIO_LEFT_0: J2.B28, J3.A28
/Compute Blade Ring Bus/CB2_GPIO_LEFT_1: J2.B29, J3.A29
/Compute Blade Ring Bus/CB2_GPIO_LEFT_2: J2.B30, J3.A30
/Compute Blade Ring Bus/CB2_GPIO_LEFT_3: J2.B31, J3.A31
/Compute Blade Ring Bus/CB2_TX_LEFT_N: J2.A26, J3.B20
/Compute Blade Ring Bus/CB2_TX_LEFT_P: J2.A25, J3.B19
/Compute Blade Ring Bus/CB2_TX_RIGHT_N: J3.B24, J4.A22
/Compute Blade Ring Bus/CB2_TX_RIGHT_P: J3.B23, J4.A21
/Compute Blade Ring Bus/CB3_GPIO_LEFT_0: J3.B28, J4.A28
/Compute Blade Ring Bus/CB3_GPIO_LEFT_1: J3.B29, J4.A29
/Compute Blade Ring Bus/CB3_GPIO_LEFT_2: J3.B30, J4.A30
/Compute Blade Ring Bus/CB3_GPIO_LEFT_3: J3.B31, J4.A31
/Compute Blade Ring Bus/CB3_TX_LEFT_N: J3.A26, J4.B20
/Compute Blade Ring Bus/CB3_TX_LEFT_P: J3.A25, J4.B19
/Compute Blade Ring Bus/CB3_TX_RIGHT_N: J4.B24, J5.A22
/Compute Blade Ring Bus/CB3_TX_RIGHT_P: J4.B23, J5.A21
/Compute Blade Ring Bus/CB4_GPIO_LEFT_0: J4.B28, J5.A28
/Compute Blade Ring Bus/CB4_GPIO_LEFT_1: J4.B29, J5.A29
/Compute Blade Ring Bus/CB4_GPIO_LEFT_2: J4.B30, J5.A30
/Compute Blade Ring Bus/CB4_GPIO_LEFT_3: J4.B31, J5.A31
/Compute Blade Ring Bus/CB4_TX_LEFT_N: J4.A26, J5.B20
/Compute Blade Ring Bus/CB4_TX_LEFT_P: J4.A25, J5.B19
/Compute Blade Ring Bus/CB4_TX_RIGHT_N: J5.B24, J6.A22
/Compute Blade Ring Bus/CB4_TX_RIGHT_P: J5.B23, J6.A21
/Compute Blade Ring Bus/CB5_GPIO_LEFT_0: J5.B28, J6.A28
/Compute Blade Ring Bus/CB5_GPIO_LEFT_1: J5.B29, J6.A29
/Compute Blade Ring Bus/CB5_GPIO_LEFT_2: J5.B30, J6.A30
/Compute Blade Ring Bus/CB5_GPIO_LEFT_3: J5.B31, J6.A31
/Compute Blade Ring Bus/CB5_TX_LEFT_N: J5.A26, J6.B20
/Compute Blade Ring Bus/CB5_TX_LEFT_P: J5.A25, J6.B19
/Compute Blade Ring Bus/CB5_TX_RIGHT_N: J6.B24, J7.A22
/Compute Blade Ring Bus/CB5_TX_RIGHT_P: J6.B23, J7.A21
/Compute Blade Ring Bus/CB6_GPIO_LEFT_0: J6.B28, J7.A28
/Compute Blade Ring Bus/CB6_GPIO_LEFT_1: J6.B29, J7.A29
/Compute Blade Ring Bus/CB6_GPIO_LEFT_2: J6.B30, J7.A30
/Compute Blade Ring Bus/CB6_GPIO_LEFT_3: J6.B31, J7.A31
/Compute Blade Ring Bus/CB6_TX_LEFT_N: J6.A26, J7.B20
/Compute Blade Ring Bus/CB6_TX_LEFT_P: J6.A25, J7.B19
/Compute Blade Ring Bus/CB6_TX_RIGHT_N: J7.B24, J8.A22
/Compute Blade Ring Bus/CB6_TX_RIGHT_P: J7.B23, J8.A21
/Compute Blade Ring Bus/CB7_GPIO_LEFT_0: J7.B28, J8.A28
/Compute Blade Ring Bus/CB7_GPIO_LEFT_1: J7.B29, J8.A29
/Compute Blade Ring Bus/CB7_GPIO_LEFT_2: J7.B30, J8.A30
/Compute Blade Ring Bus/CB7_GPIO_LEFT_3: J7.B31, J8.A31
/Compute Blade Ring Bus/CB7_TX_LEFT_N: J7.A26, J8.B20
/Compute Blade Ring Bus/CB7_TX_LEFT_P: J7.A25, J8.B19
/Compute Blade Ring Bus/CB7_TX_RIGHT_N: J1.A22, J8.B24
/Compute Blade Ring Bus/CB7_TX_RIGHT_P: J1.A21, J8.B23
/I2C IO Expander/3V3: C31.1, C32.1, C44.2, C47.1, C48.1, C49.1, C50.1, C51.1, C52.1, C53.1, C54.1, C55.1, C56.1, C57.1, C58.1, C59.1, C60.1, R38.1, R40.2, R57.1, R58.1, R67.2, U1.9, U4.2, U4.9, U11.9, U12.9, U13.1, U13.9, U14.1, U14.2, U14.9, U15.1, U15.9, U16.1, U16.9, U17.9, U18.2, U19.2, U20.9, U21.2, U21.9, U22.27, U22.31, U24.9, U25.8, U26.7, U26.8
/I2C IO Expander/CB0_LED: R60.1, U22.23
/I2C IO Expander/CB0_RESET: Q1.G1, R41.1, U22.21
/I2C IO Expander/CB1_LED: R62.1, U22.19
/I2C IO Expander/CB1_RESET: Q1.G2, R42.1, U22.22
/I2C IO Expander/CB2_LED: R64.1, U22.17
/I2C IO Expander/CB2_RESET: Q2.G1, R43.1, U22.14
/I2C IO Expander/CB3_LED: R66.1, U22.13
/I2C IO Expander/CB3_RESET: Q2.G2, R44.1, U22.16
/I2C IO Expander/CB4_LED: R59.1, U22.12
/I2C IO Expander/CB4_RESET: Q3.G1, R45.1, U22.10
/I2C IO Expander/CB5_LED: R61.1, U22.7
/I2C IO Expander/CB5_RESET: Q3.G2, R46.1, U22.11
/I2C IO Expander/CB6_LED: R63.1, U22.6
/I2C IO Expander/CB6_RESET: Q4.G1, R47.1, U22.4
/I2C IO Expander/CB7_LED: R65.1, U22.3
/I2C IO Expander/CB7_RESET: Q4.G2, R48.1, U22.5
/I2C IO Expander/I2C_SCL: J9.B5, J10.B5, J12.5, R58.2, U1.5, U4.5, U11.5, U12.2, U12.5, U13.5, U14.5, U15.5, U16.2, U16.5, U17.1, U17.5, U20.5, U21.5, U22.29, U24.2, U24.5, U25.2, U26.2
/I2C IO Expander/I2C_SDA: J9.B6, J10.B6, J12.2, R57.2, U1.4, U4.4, U11.2, U11.4, U12.4, U13.4, U14.4, U15.2, U15.4, U16.4, U17.4, U20.1, U20.4, U21.1, U21.4, U22.30, U24.1, U24.4, U25.1, U26.1
/I2C IO Expander/IEXP_ADDR: R39.1, U22.26
/I2C IO Expander/IEXP_INT_N: R40.1, U22.32
/I2C IO Expander/IEXP_RESET_N: R38.2, U22.28
/I2C IO Expander/PWREN_CB0: R49.1, U2.2, U22.24
/I2C IO Expander/PWREN_CB1: R50.1, U3.2, U22.20
/I2C IO Expander/PWREN_CB2: R51.1, U5.2, U22.18
/I2C IO Expander/PWREN_CB3: R52.1, U6.2, U22.15
/I2C IO Expander/PWREN_CB4: R53.1, U7.2, U22.9
/I2C IO Expander/PWREN_CB5: R54.1, U8.2, U22.8
/I2C IO Expander/PWREN_CB6: R55.1, U9.2, U22.2
/I2C IO Expander/PWREN_CB7: R56.1, U10.2, U22.1
/Management Blade Support/MGMT_12V0: C29.2, J9.A1, J9.A2, J9.A3, J9.B1, J9.B2, J9.B3, R36.2
/Management Blade Support/MGMT_JTAG_TCK: J9.A5, J14.6
/Management Blade Support/MGMT_JTAG_TDI: J9.A6, J14.10
/Management Blade Support/MGMT_JTAG_TDO: J9.A7, J14.8
/Management Blade Support/MGMT_JTAG_TMS: J9.A8, J14.4
/Management Blade Support/MGMT_JTAG_VDD: C45.1, J9.A9, J14.2
/Power Supply/3V3_RAW: R67.4, U23.2
/Power Supply/3V3_SHUNT_N: R67.1, U24.12
/Power Supply/3V3_SHUNT_P: R67.3, U24.11, U24.13
/Power Supply/12V0: C2.1, C4.1, C7.1, C8.1, C9.1, C10.1, C11.1, C12.1, C25.1, C26.1, C33.1, C34.1, C35.1, C36.1, C37.1, C38.1, C39.1, C40.1, C41.1, C42.1, C43.1, J12.3, R33.2, U2.3, U2.4, U2.5, U3.3, U3.4, U3.5, U5.3, U5.4, U5.5, U6.3, U6.4, U6.5, U7.3, U7.4, U7.5, U8.3, U8.4, U8.5, U9.3, U9.4, U9.5, U10.3, U10.4, U10.5, U18.3, U18.4, U18.5, U19.3, U19.4, U19.5, U23.3
/Power Supply/12V0_RAW: J11.5, J11.6, J11.7, J11.8, R33.4
/Power Supply/12V0_SHUNT_N: R33.1, U17.12
/Power Supply/12V0_SHUNT_P: R33.3, U17.11, U17.13
/Power Supply/12V_RAW_CB0: R18.4, U2.6, U2.7, U2.8
/Power Supply/12V_RAW_CB1: R20.4, U3.6, U3.7, U3.8
/Power Supply/12V_RAW_CB2: R27.4, U5.6, U5.7, U5.8
/Power Supply/12V_RAW_CB3: R28.4, U6.6, U6.7, U6.8
/Power Supply/12V_RAW_CB4: R29.4, U7.6, U7.7, U7.8
/Power Supply/12V_RAW_CB5: R30.4, U8.6, U8.7, U8.8
/Power Supply/12V_RAW_CB6: R31.4, U9.6, U9.7, U9.8
/Power Supply/12V_RAW_CB7: R32.4, U10.6, U10.7, U10.8
/Power Supply/12V_RAW_MGMT: R36.4, U18.6, U18.7, U18.8
/Power Supply/12V_RAW_SWITCH: R37.4, U19.6, U19.7, U19.8
/Power Supply/CB0_SHUNT_N: R18.1, U1.12
/Power Supply/CB0_SHUNT_P: R18.3, U1.11, U1.13
/Power Supply/CB1_SHUNT_N: R20.1, U4.12
/Power Supply/CB1_SHUNT_P: R20.3, U4.11, U4.13
/Power Supply/CB2_SHUNT_N: R27.1, U11.12
/Power Supply/CB2_SHUNT_P: R27.3, U11.11, U11.13
/Power Supply/CB3_SHUNT_N: R28.1, U12.12
/Power Supply/CB3_SHUNT_P: R28.3, U12.11, U12.13
/Power Supply/CB4_SHUNT_N: R29.1, U13.12
/Power Supply/CB4_SHUNT_P: R29.3, U13.11, U13.13
/Power Supply/CB5_SHUNT_N: R30.1, U14.12
/Power Supply/CB5_SHUNT_P: R30.3, U14.11, U14.13
/Power Supply/CB6_SHUNT_N: R31.1, U15.12
/Power Supply/CB6_SHUNT_P: R31.3, U15.11, U15.13
/Power Supply/CB7_SHUNT_N: R32.1, U16.12
/Power Supply/CB7_SHUNT_P: R32.3, U16.11, U16.13
/Power Supply/MGMT_SHUNT_N: R36.1, U20.12
/Power Supply/MGMT_SHUNT_P: R36.3, U20.11, U20.13
/Power Supply/SWITCH_12V0: C30.2, J10.A1, J10.A2, J10.A3, J10.B1, J10.B2, J10.B3, R37.2
/Power Supply/SWITCH_SHUNT_N: R37.1, U21.12
/Power Supply/SWITCH_SHUNT_P: R37.3, U21.11, U21.13
/Switch Blade Support/SWITCH_JTAG_TCK: J10.A5, J13.6
/Switch Blade Support/SWITCH_JTAG_TDI: J10.A6, J13.10
/Switch Blade Support/SWITCH_JTAG_TDO: J10.A7, J13.8
/Switch Blade Support/SWITCH_JTAG_TMS: J10.A8, J13.4
/Switch Blade Support/SWITCH_JTAG_VDD: C46.1, J10.A9, J13.2
unnamed: C1.2, U2.1
unnamed: C5.2, U3.1
unnamed: C13.2, U5.1
unnamed: C14.2, U6.1
unnamed: C15.2, U7.1
unnamed: C16.2, U8.1
unnamed: C17.2, U9.1
unnamed: C18.2, U10.1
unnamed: C27.2, U18.1
unnamed: C28.2, U19.1
unnamed: D1.2, R60.2
unnamed: D2.2, R62.2
unnamed: D3.2, R64.2
unnamed: D4.2, R66.2
unnamed: D5.2, R59.2
unnamed: D6.2, R61.2
unnamed: D7.2, R63.2
unnamed: D8.2, R65.2
unnamed: R17.1, U2.10
unnamed: R19.1, U3.10
unnamed: R21.1, U5.10
unnamed: R22.1, U6.10
unnamed: R23.1, U7.10
unnamed: R24.1, U8.10
unnamed: R25.1, U9.10
unnamed: R26.1, U10.10
unnamed: R34.1, U18.10
unnamed: R35.1, U19.10

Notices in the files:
legacy-branches/old-pcb/usb-hub-eurocard/usb-hub-eurocard.kicad_pcb:
Schematic & layout are BSD licensed. Silk logos by W. Lain.
